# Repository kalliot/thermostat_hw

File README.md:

# thermostat_hw
Kicad data for thermostat hardware

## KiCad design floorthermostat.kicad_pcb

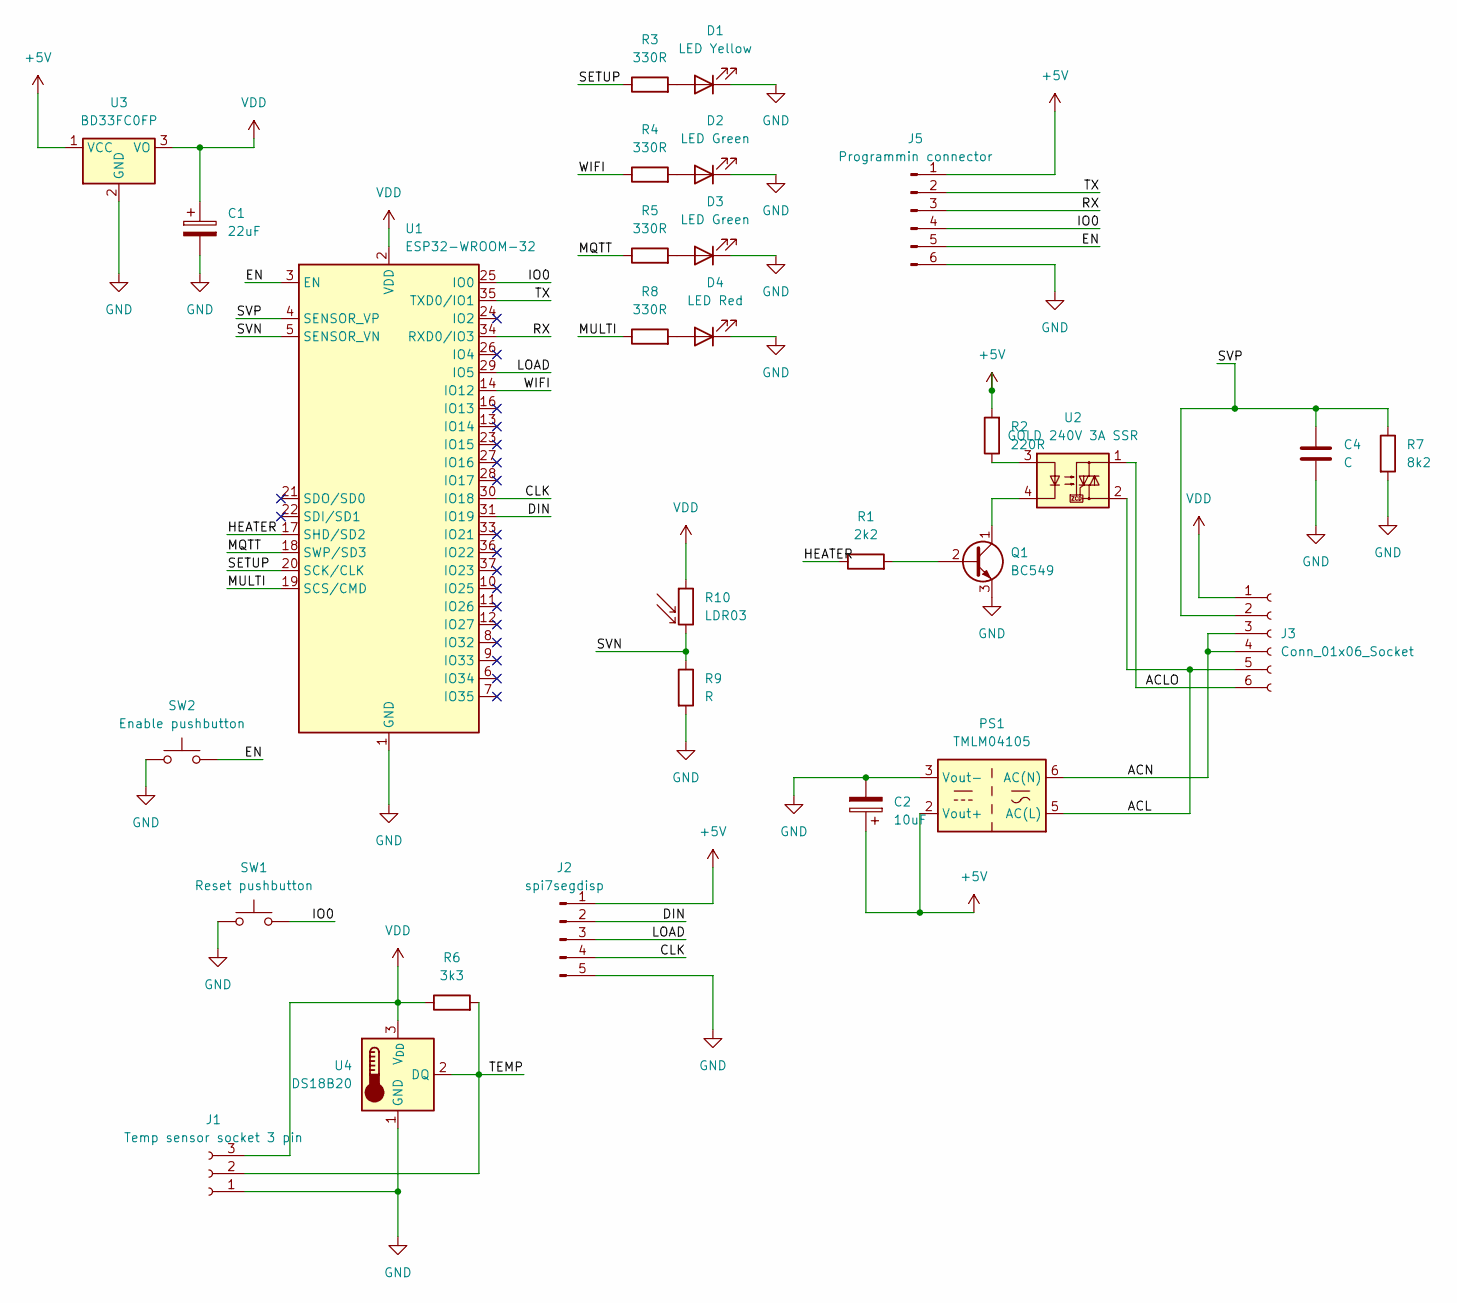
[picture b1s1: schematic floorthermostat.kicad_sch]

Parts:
C1: 22uF; CP_Axial_L10.0mm_D4.5mm_P15.00mm_Horizontal
C2: 10uF; CP_Axial_L10.0mm_D4.5mm_P15.00mm_Horizontal
C4: C; CP_Axial_L10.0mm_D6.0mm_P15.00mm_Horizontal
D1: LED Yellow; LED_D5.0mm
D2, D3: LED Green; LED_D5.0mm
D4: LED Red; LED_D5.0mm
J1: Temp sensor socket 3 pin; PinSocket_1x03_P2.54mm_Horizontal
J2: spi7segdisp; PinHeader_1x05_P2.54mm_Vertical
J3: Conn_01x06_Socket; TerminalBlock_Phoenix_MKDS-1,5-6-5.08_1x06_P5.08mm_Horizont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
J5: Programmin connector; PinHeader_1x06_P2.54mm_Vertical
PS1: TMLM04105; china_5v_acdc
Q1: BC549; TO-92_Inline
R1: 2k2; R_Axial_DIN0207_L6.3mm_D2.5mm_P15.24mm_Horizontal
R2: 220R; R_Axial_DIN0207_L6.3mm_D2.5mm_P15.24mm_Horizontal
R3, R4, R5, R8: 330R; R_Axial_DIN0207_L6.3mm_D2.5mm_P15.24mm_Horizontal
R6: 3k3; R_Axial_DIN0207_L6.3mm_D2.5mm_P15.24mm_Horizontal
R7: 8k2; R_Axial_DIN0207_L6.3mm_D2.5mm_P15.24mm_Horizontal
R9: R; R_Axial_DIN0207_L6.3mm_D2.5mm_P15.24mm_Horizontal
R10: LDR03; R_LDR_10x8.5mm_P7.6mm_Vertical
SW1: Reset pushbutton; SW_PUSH_6mm_H5mm
SW2: Enable pushbutton; SW_PUSH_6mm_H5mm
U1: ESP32-WROOM-32
U2: GOLD 240V 3A SSR; Relay_GOLD_3A
U3: BD33FC0FP; TO-262-3_Vertical
U4: DS18B20; TO-92_Inline

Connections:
+5V: C2.1, J2.1, J5.1, PS1.2 (Vout+), R2.2, U3.1 (VCC)
/ACL: J3.5, PS1.5 (AC(L)), U2.2
/ACLO: J3.6, U2.1
/ACN: J3.3, J3.4, PS1.6 (AC(N))
/CLK: J2.4, U1.30 (IO18)
/DIN: J2.2, U1.31 (IO19)
/EN: J5.5, SW2.2, U1.3 (EN)
/HEATER: R1.1, U1.17 (SHD/SD2)
/IO0: J5.4, SW1.2, U1.25 (IO0)
/LOAD: J2.3, U1.29 (IO5)
/MQTT: R5.1, U1.18 (SWP/SD3)
/MULTI: R8.1, U1.19 (SCS/CMD)
/RX: J5.3, U1.34 (RXD0/IO3)
/SETUP: R3.1, U1.20 (SCK/CLK)
/SVN: R9.1, R10.2, U1.5 (SENSOR_VN)
/SVP: C4.1, J3.2, R7.1, U1.4 (SENSOR_VP)
/TEMP: J1.2, R6.2, U4.2 (DQ)
/TX: J5.2, U1.35 (TXD0/IO1)
/WIFI: R4.1, U1.14 (IO12)
GND: C1.2, C2.2, C4.2, D1.1 (K), D2.1 (K), D3.1 (K), D4.1 (K), J1.1, J2.5, J5.6, PS1.3 (Vout-), Q1.3 (E), R7.2, R9.2, SW1.1, SW2.1, U1.1 (GND), U1.15 (GND), U1.38 (GND), U1.39 (GND), U3.2 (GND), U4.1 (GND)
unnamed: D1.2 (A), R3.2
unnamed: D2.2 (A), R4.2
unnamed: D3.2 (A), R5.2
unnamed: D4.2 (A), R8.2
unnamed: Q1.2 (B), R1.2
unnamed: Q1.1 (C), U2.4
unnamed: R2.1, U2.3
VDD: C1.1, J1.3, J3.1, R6.1, R10.1, U1.2 (VDD), U3.3 (VO), U4.3 (V_{DD})

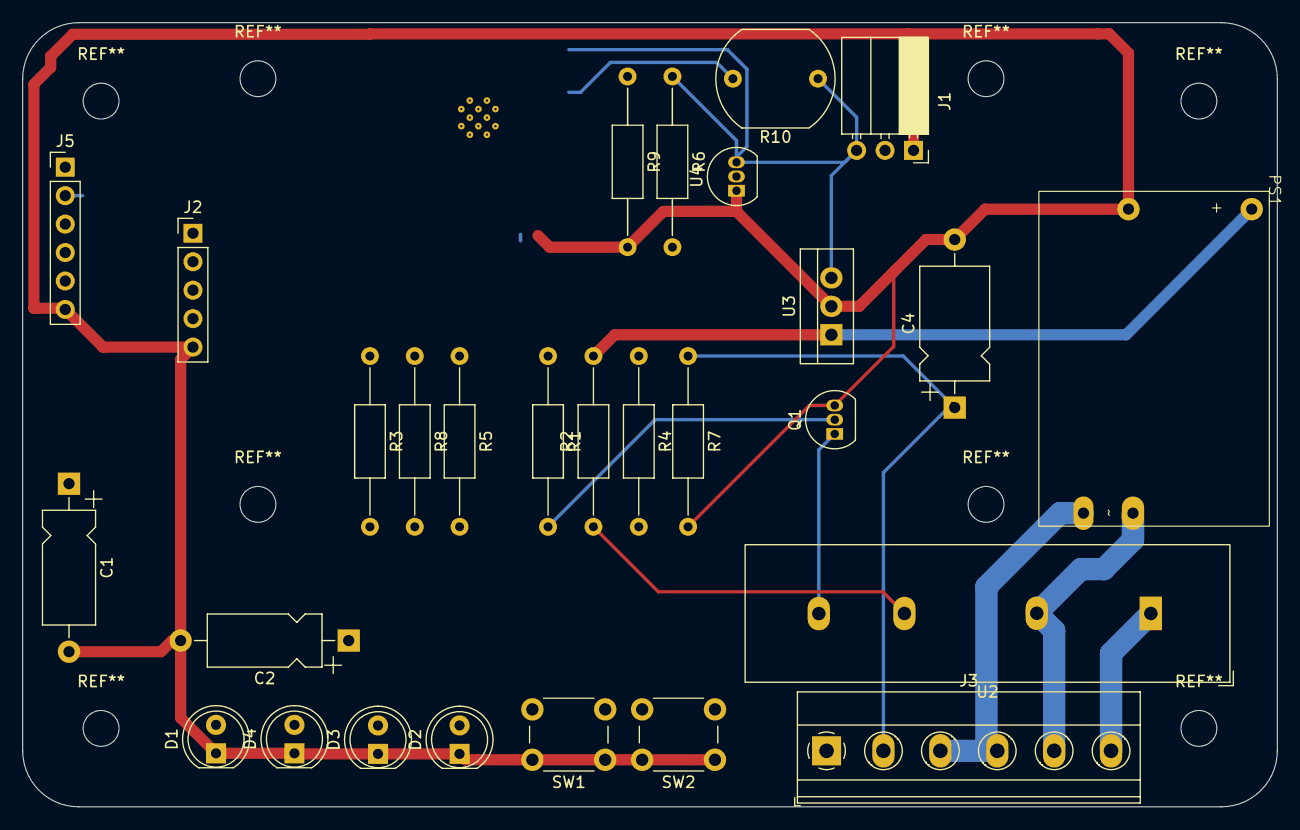
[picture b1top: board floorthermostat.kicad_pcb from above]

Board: 2 copper layers, 112.0 x 70.0 mm, 29 parts (1 on the bottom side), 28 nets.

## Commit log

2024-09-24 Added labels for esp, about the spi display.
2024-09-25 Added ldr for display brightness control.
2025-01-17 fixed ssr control bug. Added 2 filtering capasitors. Defined some component footprints.
2025-01-28 Added many footprints.
2025-01-29 Created footprint for GOLD_SSR_3A relay. Added 6 pin screw header for ac, heater and ntc.
2025-02-13 Checked all the component footprints.
2025-02-20 Started designing the pcb.
2025-03-04 Sketching component positions to pcb.
2025-04-23 Changed pcb to dual-sided.
